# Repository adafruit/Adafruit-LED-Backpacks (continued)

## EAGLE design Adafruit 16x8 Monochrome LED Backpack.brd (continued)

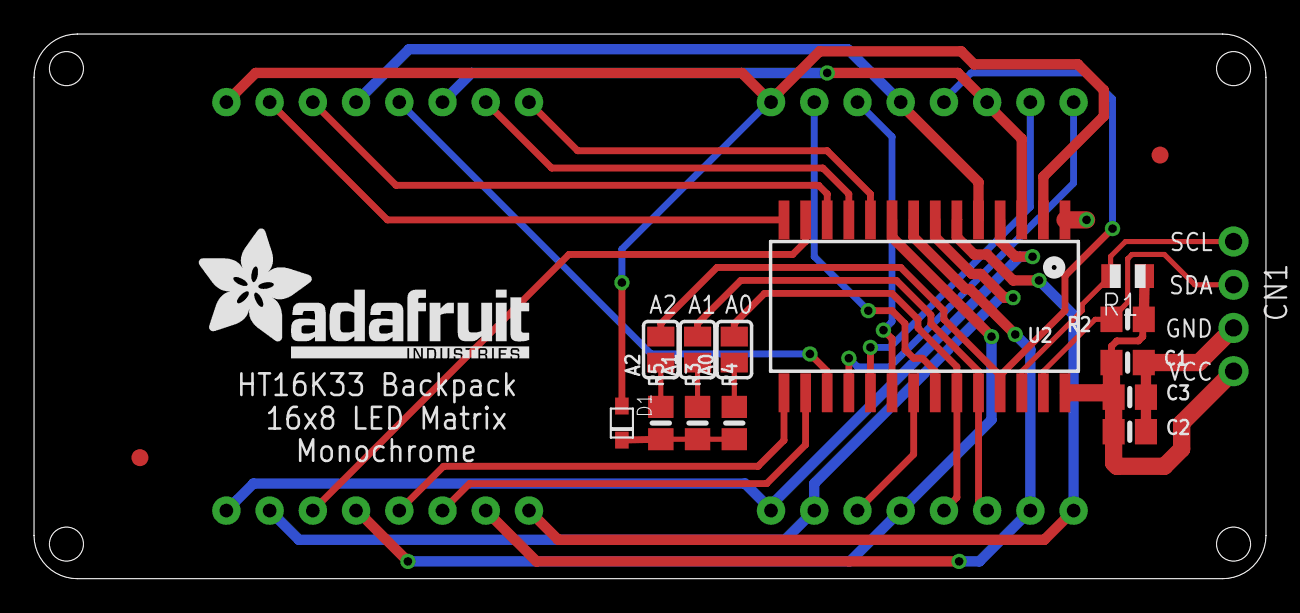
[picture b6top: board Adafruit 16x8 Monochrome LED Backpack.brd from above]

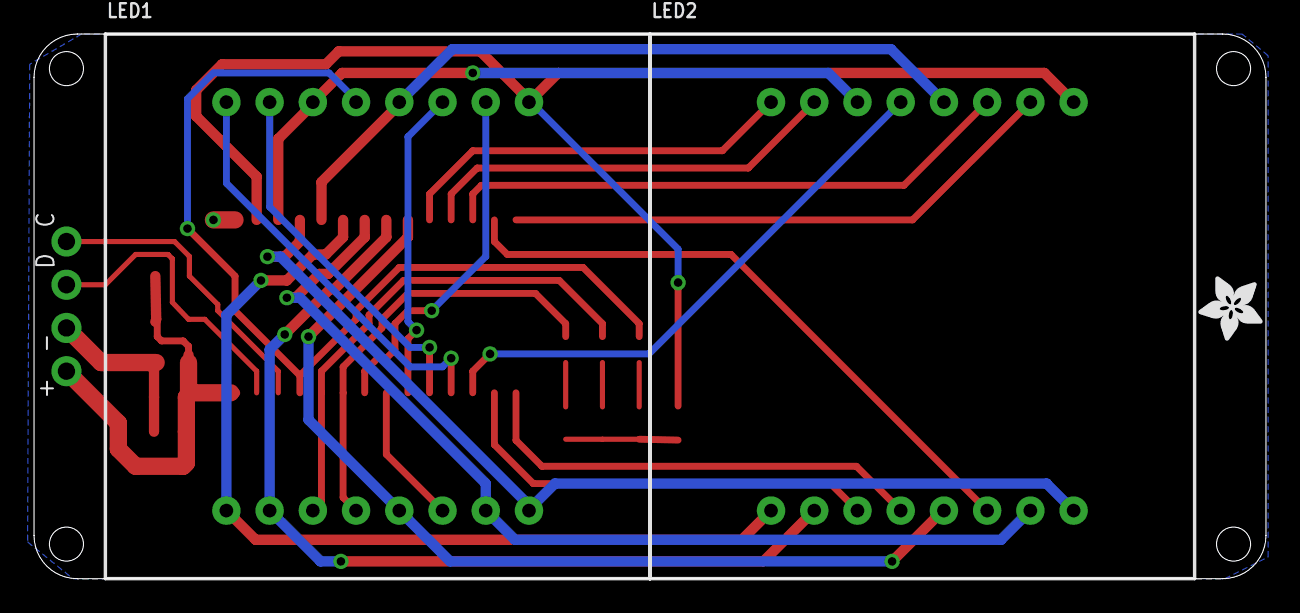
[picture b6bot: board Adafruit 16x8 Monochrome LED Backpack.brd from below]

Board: 2 copper layers, 72.4 x 32.0 mm, 20 parts (3 on the bottom side), 32 nets.

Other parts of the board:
U$3: ADAFRUIT_TEXT_20MM
U$4: ADAFRUIT_3.5MM

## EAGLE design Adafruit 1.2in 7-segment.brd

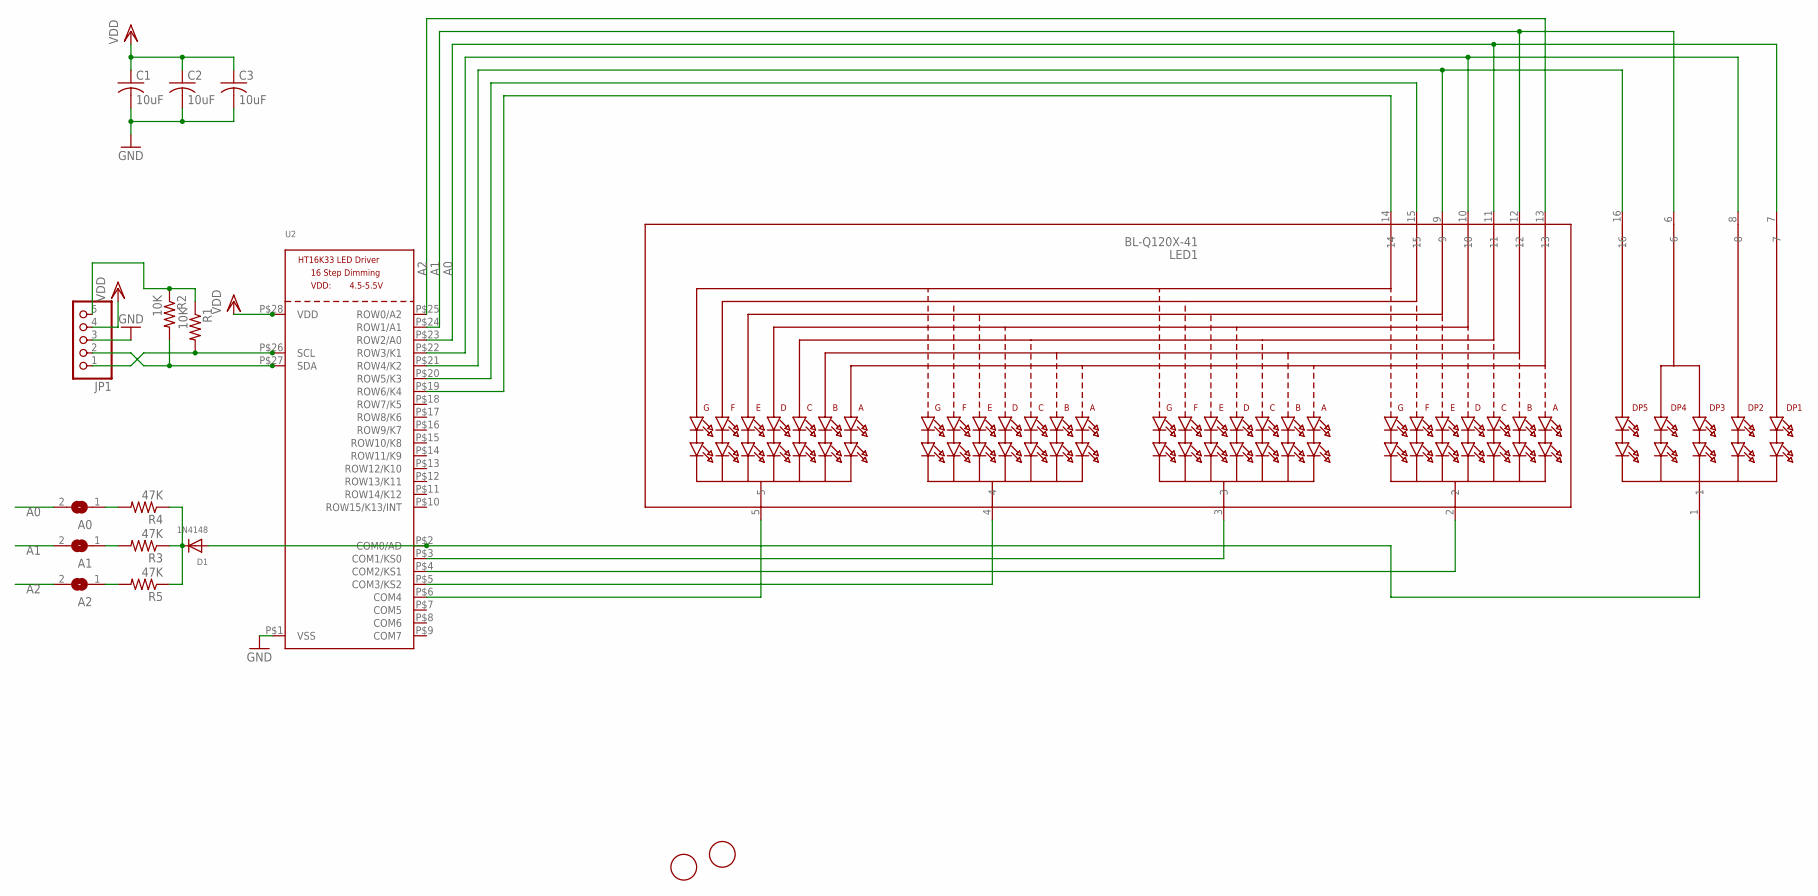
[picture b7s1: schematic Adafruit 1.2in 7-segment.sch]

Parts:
A0, A1, A2: SOLDERJUMPERREFLOW_NOPASTE; SOLDERJUMPER_REFLOW_NOPASTE
C1, C2, C3: 10uF; C0805K
D1: 1N4148; SOD-323F
JP1: HEADER-1X576MIL; 1X05_ROUND_76
LED1: BL-Q120X-41; SEGMENT_BL-Q120A
R1, R2: 10K; R0805
R3, R4, R5: 47K; R0805
U2: HT16K33_SOP28; SOP28_300MIL
U$1, U$2: FIDUCIAL; FIDUCIAL_1MM

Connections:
A0: A0.2, LED1.7, LED1.11, U2.P$23 (ROW2/A0)
A1: A1.2, LED1.6, LED1.12, U2.P$24 (ROW1/A1)
A2: A2.2, LED1.13, U2.P$25 (ROW0/A2)
GND: C1.2, C2.2, C3.2, JP1.3, U2.P$1 (VSS)
unnamed: D1.C, R3.1, R4.1, R5.1
unnamed: D1.A, LED1.1, U2.P$2 (COM0/AD)
unnamed: LED1.3, U2.P$3 (COM1/KS0)
unnamed: LED1.4, U2.P$5 (COM3/KS2)
unnamed: LED1.5, U2.P$6 (COM4)
unnamed: LED1.2, U2.P$4 (COM2/KS1)
unnamed: A2.1, R5.2
unnamed: JP1.5, R1.1, R2.1
unnamed: LED1.8, LED1.10, U2.P$22 (ROW3/K1)
unnamed: LED1.9, LED1.16, U2.P$21 (ROW4/K2)
unnamed: LED1.15, U2.P$20 (ROW5/K3)
unnamed: LED1.14, U2.P$19 (ROW6/K4)
unnamed: A1.1, R3.2
unnamed: A0.1, R4.2
SCL: JP1.1, R1.2, U2.P$26 (SCL)
SDA: JP1.2, R2.2, U2.P$27 (SDA)
VDD: C1.1, C2.1, C3.1, JP1.4, U2.P$28 (VDD)

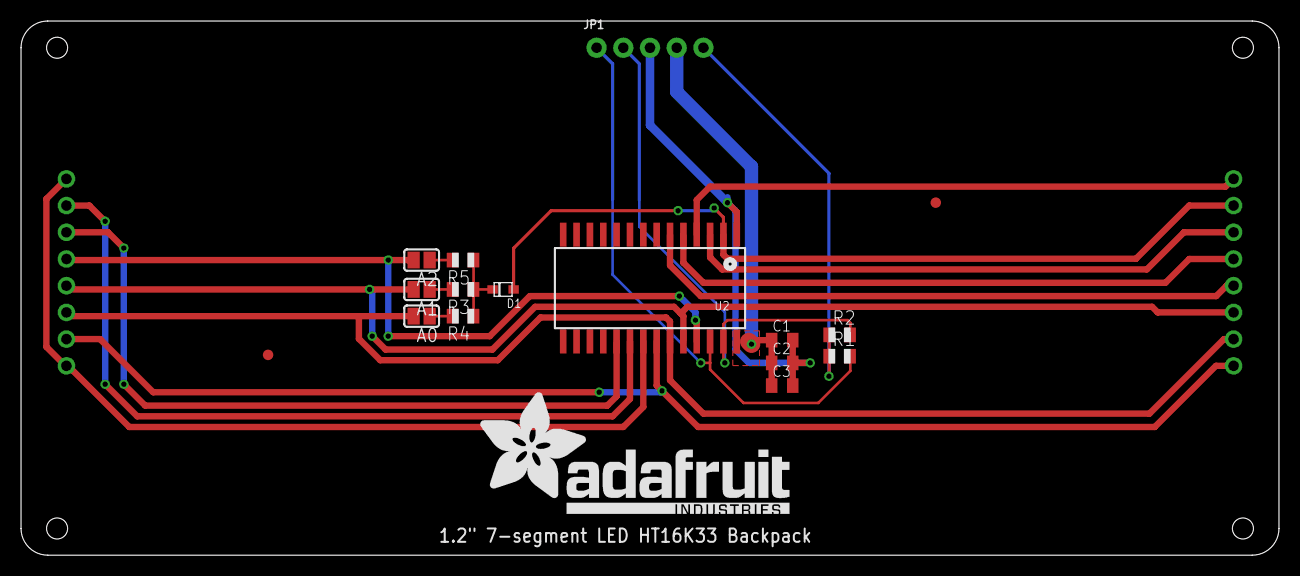
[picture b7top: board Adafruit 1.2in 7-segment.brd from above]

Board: 2 copper layers, 119.6 x 50.8 mm, 18 parts (1 on the bottom side), 21 nets.

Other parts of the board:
U$3: ADAFRUIT_TEXT_30MM

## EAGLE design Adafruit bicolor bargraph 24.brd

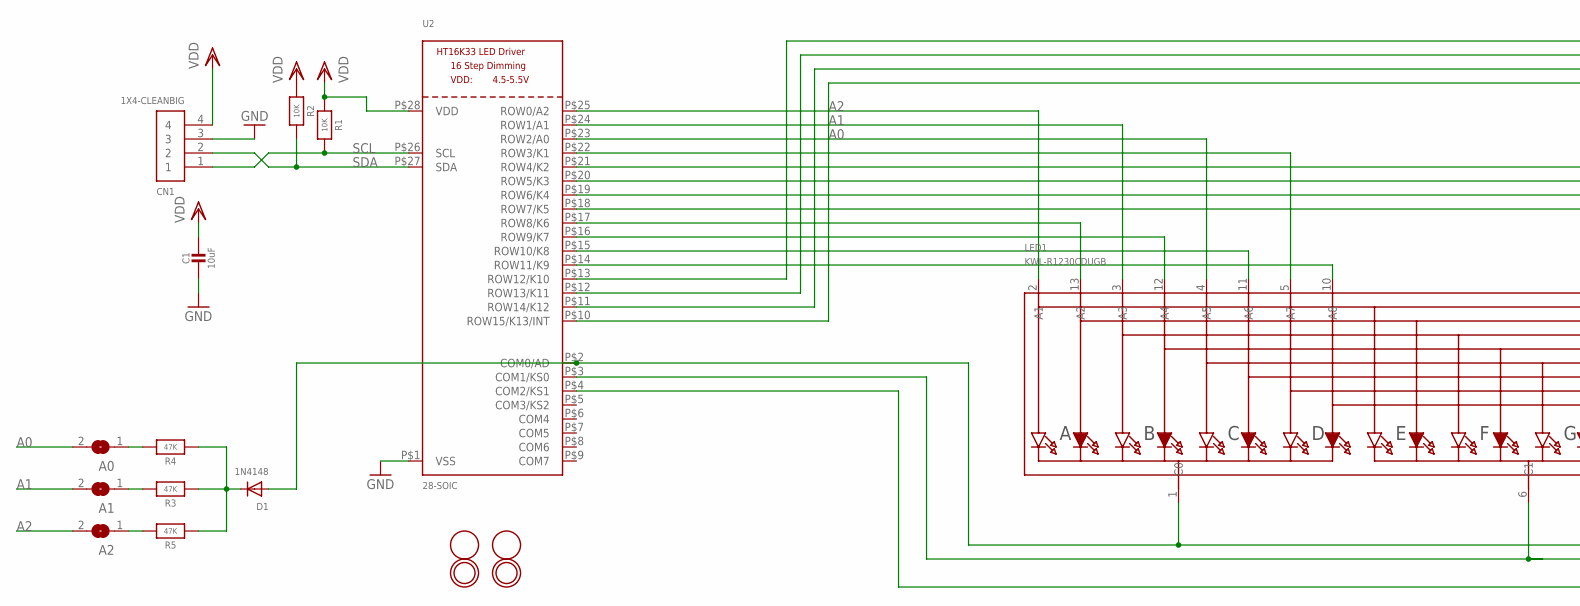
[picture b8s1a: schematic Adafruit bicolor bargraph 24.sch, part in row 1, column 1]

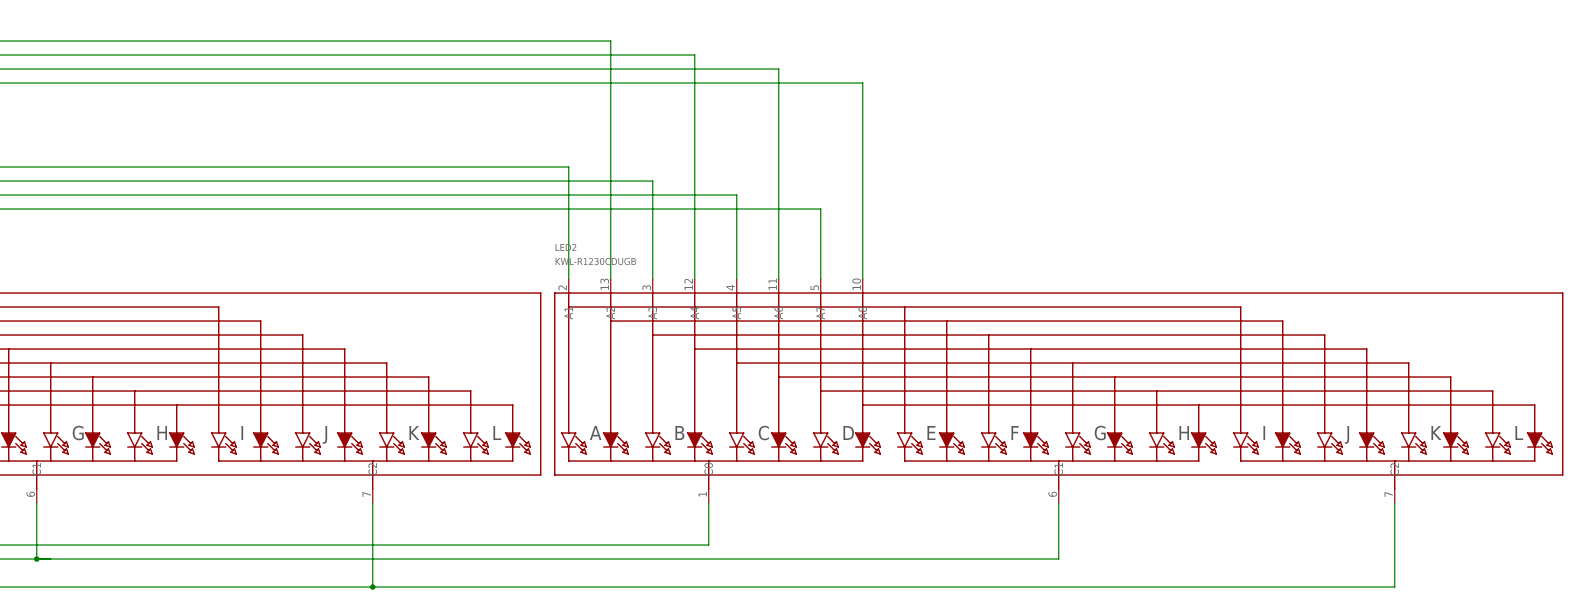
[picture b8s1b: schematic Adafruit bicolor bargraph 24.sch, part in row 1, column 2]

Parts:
A0, A1, A2: SOLDERJUMPERREFLOW_NOPASTE; SOLDERJUMPER_REFLOW_NOPASTE
C1: 10uF; 0805-NO
CN1: 1X4-CLEANBIG; 1X04-CLEANBIG
D1: 1N4148; SOD-323F
LED1, LED2: KWL-R1230CDUGB; SEGMENT_BICOL_BL-AR12Z3010
R1, R2: 10K; 0805-NO
R3, R4, R5: 47K; 0805-NO
U2: 28-SOIC; SOP28_300MIL
U$1, U$2: FIDUCIAL; FIDUCIAL_1MM
U$3, U$4: MOUNTINGHOLE2.5; MOUNTINGHOLE_2.5_PLATED

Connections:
A0: A0.2, LED1.4 (A5), U2.P$23 (ROW2/A0)
A1: A1.2, LED1.3 (A3), U2.P$24 (ROW1/A1)
A2: A2.2, LED1.2 (A1), U2.P$25 (ROW0/A2)
C0: D1.A, LED1.1 (C0), LED2.1 (C0), U2.P$2 (COM0/AD)
C1: LED1.6 (C1), LED2.6 (C1), U2.P$3 (COM1/KS0)
C2: LED1.7 (C2), LED2.7 (C2), U2.P$4 (COM2/KS1)
GND: C1.2, CN1.3, U2.P$1 (VSS)
unnamed: LED2.5 (A7), U2.P$18 (ROW7/K5)
unnamed: LED1.13 (A2), U2.P$17 (ROW8/K6)
unnamed: LED2.4 (A5), U2.P$19 (ROW6/K4)
unnamed: A2.1, R5.2
unnamed: D1.C, R3.1, R4.1, R5.1
unnamed: A1.1, R3.2
unnamed: A0.1, R4.2
unnamed: LED2.2 (A1), U2.P$21 (ROW4/K2)
unnamed: LED1.5 (A7), U2.P$22 (ROW3/K1)
unnamed: LED2.3 (A3), U2.P$20 (ROW5/K3)
unnamed: LED1.12 (A4), U2.P$16 (ROW9/K7)
R10: LED1.11 (A6), U2.P$15 (ROW10/K8)
R11: LED1.10 (A8), U2.P$14 (ROW11/K9)
R12: LED2.13 (A2), U2.P$13 (ROW12/K10)
R13: LED2.12 (A4), U2.P$12 (ROW13/K11)
R14: LED2.11 (A6), U2.P$11 (ROW14/K12)
R15: LED2.10 (A8), U2.P$10 (ROW15/K13/INT)
SCL: CN1.1, R1.2, U2.P$26 (SCL)
SDA: CN1.2, R2.2, U2.P$27 (SDA)
VDD: C1.1, CN1.4, R1.1, R2.1, U2.P$28 (VDD)

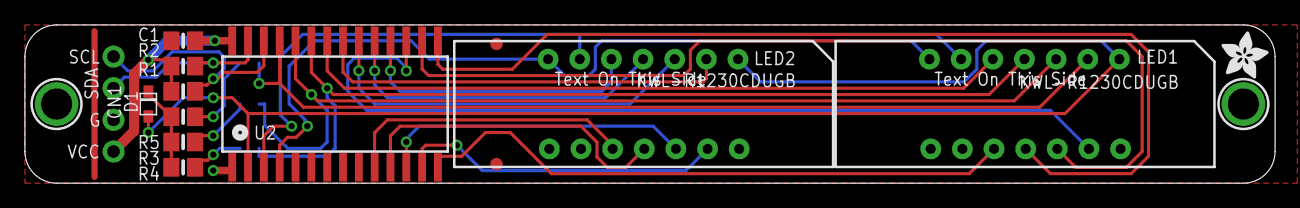
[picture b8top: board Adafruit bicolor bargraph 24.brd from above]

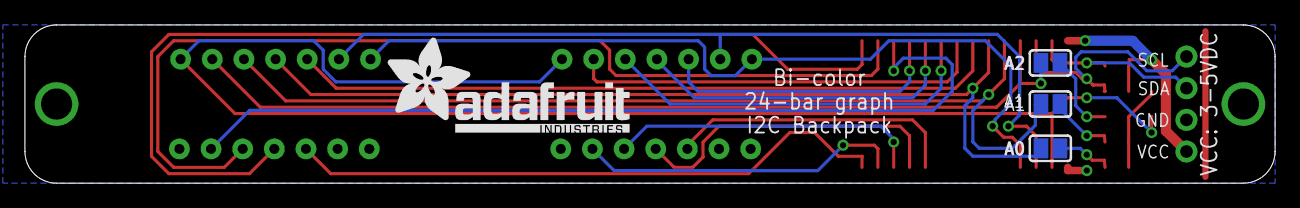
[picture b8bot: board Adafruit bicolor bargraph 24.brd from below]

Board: 2 copper layers, 100.3 x 12.7 mm, 20 parts (4 on the bottom side), 27 nets.

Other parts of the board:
U$5: ADAFRUIT_TEXT_20MM
U$6: ADAFRUIT_3.5MM

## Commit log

2012-06-13 init
2012-06-13 readme
2013-09-30 bicolor
2014-04-23 bicolor bargraphs!
2014-05-26 1.2" version
2014-07-22 BIG ones
2014-11-16 added quad alphanum
2015-04-05 yeah!
2015-05-26 add breakout
2022-02-04 Added 0.56 QT files
2022-08-23 Add board files for 0.54 14-segment QT version.
2023-02-13 adding bicolor STEMMA files
2023-11-06 Update 1.2-inch 8x8 backpack files
